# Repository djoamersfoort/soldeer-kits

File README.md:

# Soldeer-kits
In deze repo verzamelen we schakelingen voor soldeerprojectjes bij de DJO.

## Bestanden en mappen

Voor het tekenen van de schema's wordt het programma [KiCad](https://kicad-pcb.org/) gebruikt. Uitleg over dit programma is te vinden op de website van [Sparkfun](https://learn.sparkfun.com/tutorials/beginners-guide-to-kicad/all#running-design-rule-check). 

De bestanden van diverse schakelingen staan in de map "*schakelingen*" (verrassing). Deze zullen vooral onderdelen uit de KiCad standaard bibliotheek gebruiken. Echter bestaan er ook componenten die daar niet te vinden zijn. Hiervoor houden we een eigen bibliotheek bij in de map "*bibliotheek*". Is iets echt alleen nuttig voor je eigen project? Dan kan je dat in de "schakelingen"-map bijvoegen.

## Zelf een leuke schakeling gevonden?

Heb je zelf een leuke schakeling gevonden? Deel deze dan vooral met ons. Informeer even bij een van de begeleiders over hoe samen te werken met Git. 

### Spelregels:

### Voor deze repository gelden een aantal spelregels.

- Creëer een nieuw mapje in de "*schakelingen*" voor elke nieuwe schakeling
- Vermeld de bron waar je de schakeling gevonden hebt (in het schema)
- Overleg even voor het toevoegen van nieuwe componenten in de bibliotheek
- Het is **niet** de bedoeling om schakelingen van commerciële kits te kopiëren

## Componentselectie

Het is natuurlijk het leuikst als andere DJO-ers de schakeling ook kunnen bouwen. Wat we allemaal hebben liggen is te vinden in de [onderdelenzoekmachine](https://www.djoamersfoort.nl/zoekmachine/). Als er meerdere versies van een onderdeel zijn, vermeld dan het volledige typenummer in het schema.

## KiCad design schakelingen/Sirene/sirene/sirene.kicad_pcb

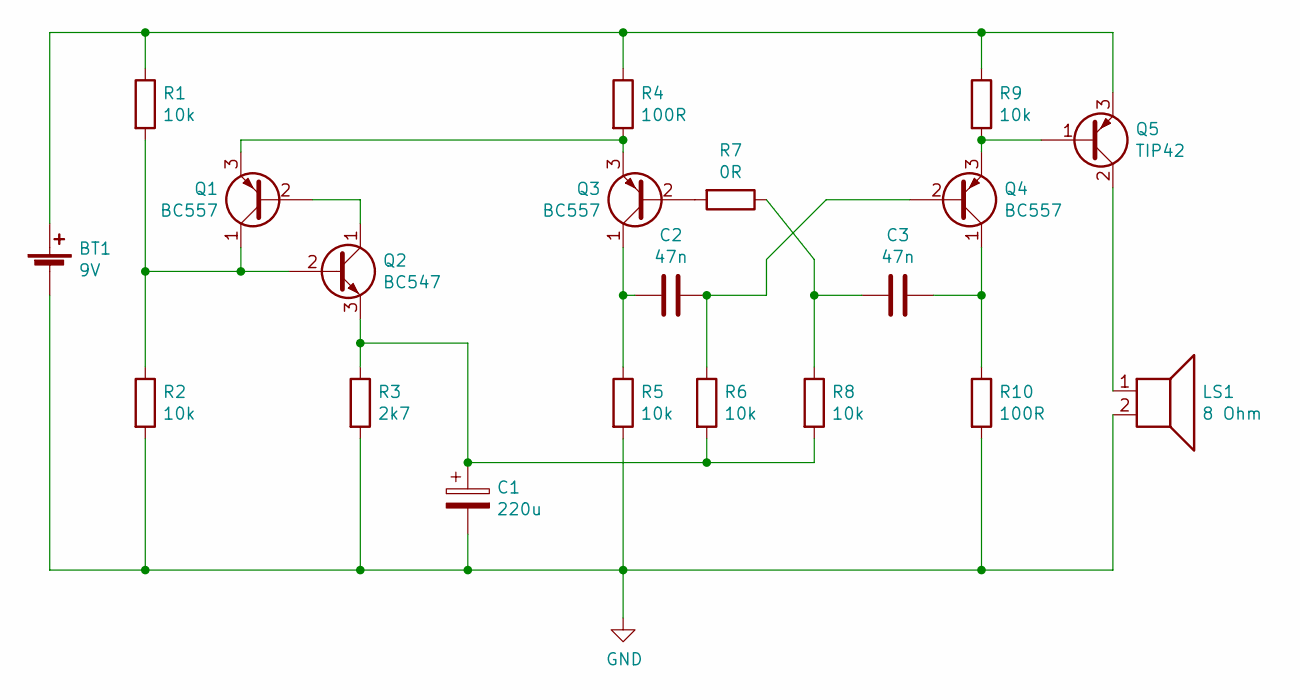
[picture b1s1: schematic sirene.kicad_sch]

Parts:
BT1: 9V; 9v batterij
C1: 220u; CP_Axial_L20.0mm_D10.0mm_P26.00mm_Horizontal
C2, C3: 47n; C_Rect_L7.2mm_W2.5mm_P5.00mm_FKS2_FKP2_MKS2_MKP2
LS1: 8 Ohm; PinHeader_1x02_P2.54mm_Vertical
Q1, Q3, Q4: BC557; TO-92_Wide
Q2: BC547; TO-92_Wide
Q5: TIP42; TO-92_Wide
R1, R2, R5, R6, R8, R9: 10k; R_Axial_DIN0207_L6.3mm_D2.5mm_P7.62mm_Horizontal
R3: 2k7; R_Axial_DIN0207_L6.3mm_D2.5mm_P7.62mm_Horizontal
R4, R10: 100R; R_Axial_DIN0207_L6.3mm_D2.5mm_P7.62mm_Horizontal
R7: 0R; R_Axial_DIN0207_L6.3mm_D2.5mm_P7.62mm_Horizontal

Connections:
GND: BT1.2 (-), C1.2, LS1.2, R2.2, R3.2, R5.2, R10.2
unnamed: BT1.1 (+), Q5.3 (E), R1.1, R4.1, R9.1
unnamed: C1.1, Q2.3 (E), R3.1, R6.2, R8.2
unnamed: C2.1, Q4.2 (B), R6.1
unnamed: C2.2, Q3.1 (C), R5.1
unnamed: C3.1, Q4.1 (C), R10.1
unnamed: C3.2, R7.1, R8.1
unnamed: LS1.1, Q5.2 (C)
unnamed: Q1.1 (C), Q2.2 (B), R1.2, R2.1
unnamed: Q1.2 (B), Q2.1 (C)
unnamed: Q1.3 (E), Q3.3 (E), R4.2
unnamed: Q3.2 (B), R7.2
unnamed: Q4.3 (E), Q5.1 (B), R9.2

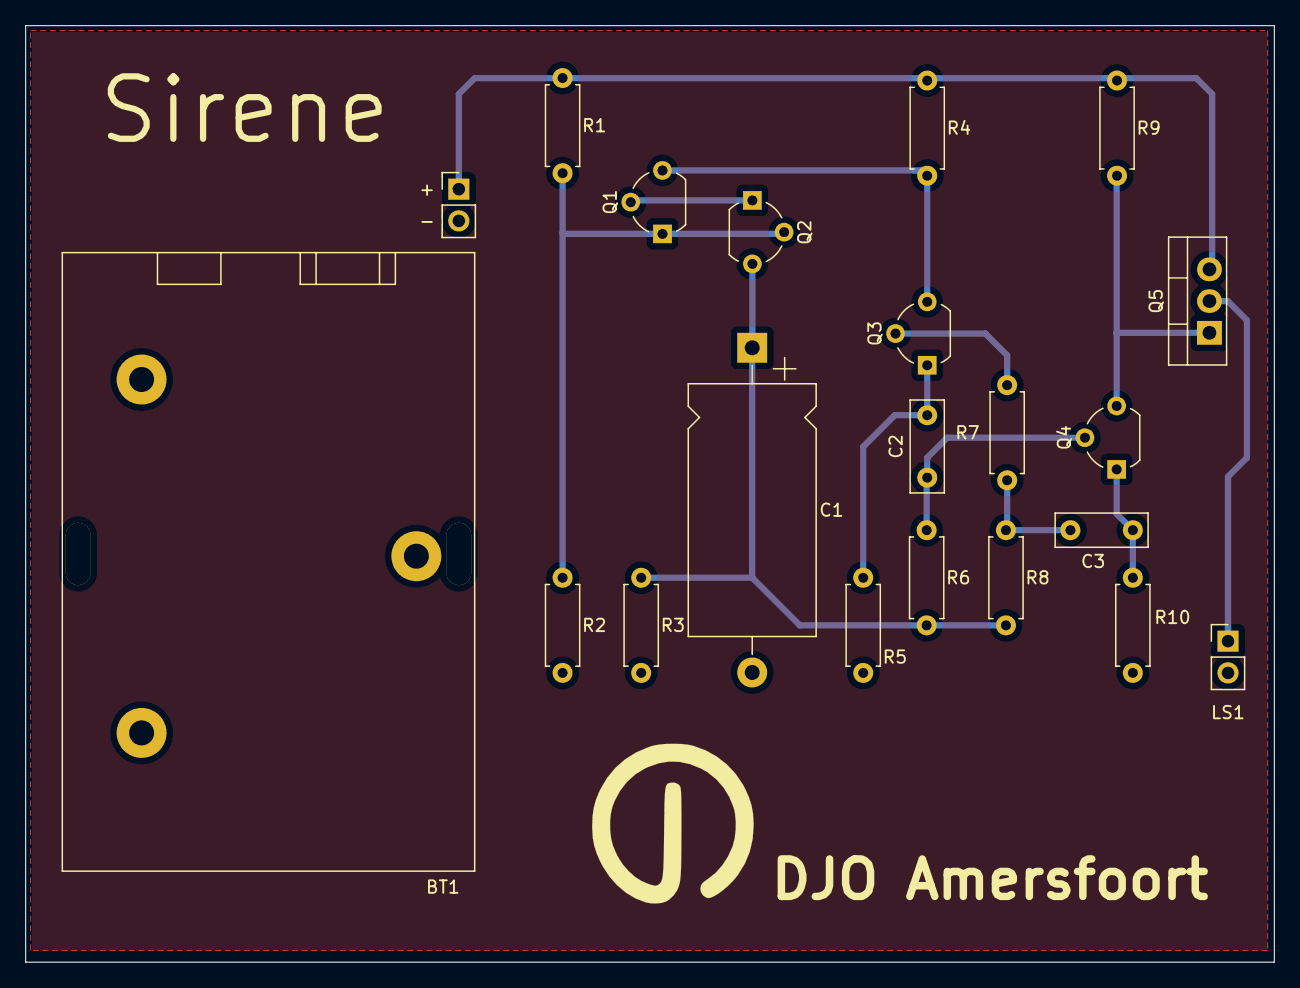
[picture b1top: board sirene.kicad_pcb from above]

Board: 2 copper layers, 100.0 x 75.0 mm, 20 parts (0 on the bottom side), 13 nets.

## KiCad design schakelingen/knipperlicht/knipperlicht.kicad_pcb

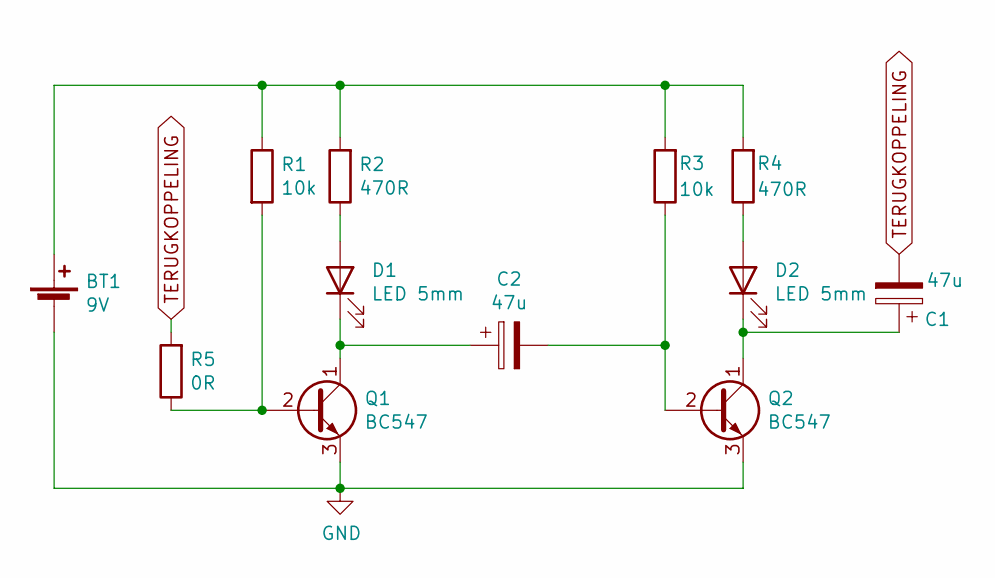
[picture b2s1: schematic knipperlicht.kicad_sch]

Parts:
BT1: 9V; 9v batterij
C1, C2: 47u; CP_Radial_D5.0mm_P2.00mm
D1, D2: LED 5mm; LED_D5.0mm_Clear
Q1, Q2: BC547; TO-92_Wide
R1, R3: 10k; R_Axial_DIN0207_L6.3mm_D2.5mm_P7.62mm_Horizontal
R2, R4: 470R; R_Axial_DIN0207_L6.3mm_D2.5mm_P7.62mm_Horizontal
R5: 0R; R_Axial_DIN0207_L6.3mm_D2.5mm_P7.62mm_Horizontal

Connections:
GND: BT1.2 (-), Q1.3 (E), Q2.3 (E)
unnamed: BT1.1 (+), R1.1, R2.2, R3.2, R4.2
unnamed: C1.1, D2.1 (K), Q2.1 (C)
unnamed: C2.1, D1.1 (K), Q1.1 (C)
unnamed: C2.2, Q2.2 (B), R3.1
unnamed: D1.2 (A), R2.1
unnamed: D2.2 (A), R4.1
unnamed: Q1.2 (B), R1.2, R5.1
TERUGKOPPELING: C1.2, R5.2

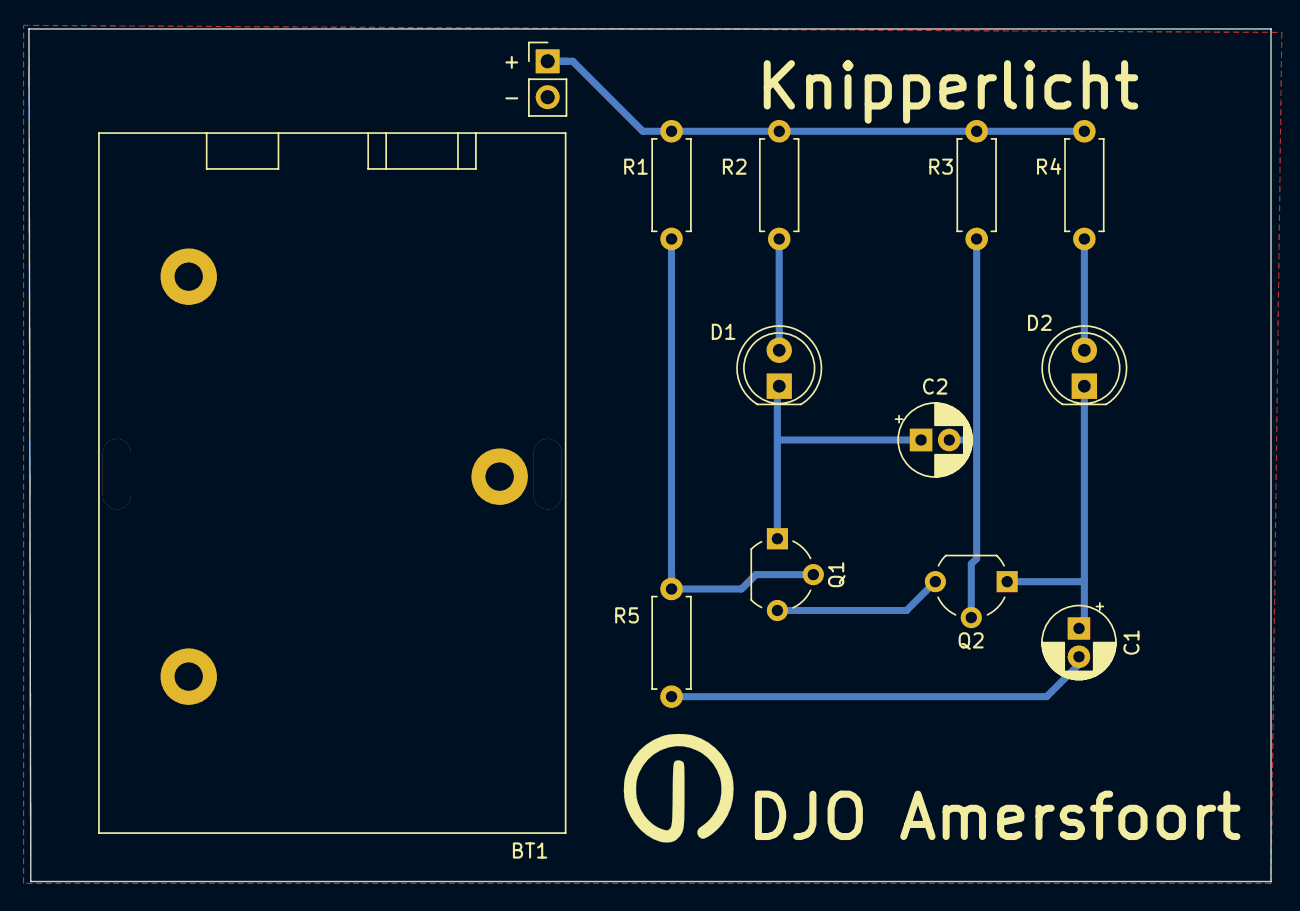
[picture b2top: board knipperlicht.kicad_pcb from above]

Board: 2 copper layers, 87.9 x 60.3 mm, 12 parts (0 on the bottom side), 9 nets.

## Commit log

2020-06-13 Test 123
2020-06-13 add test
2020-06-13 Sirene schema toegevoegd
2020-08-08 Sirene PCB layout.
2020-08-08 Readme. 9V batterij in bibliotheek. Knipperlicht toegevoegd.
2023-07-01 Footprint van transistoren knipperlicht bijgewerkt voor handsolderen
2023-07-22 Footprint van sirene bijgewerkt voor handsolderen.
2023-07-22 Footprint Q5 sirene veranderd naar TO-220
